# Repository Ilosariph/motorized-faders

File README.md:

# Motorized Fader Controller

RP2040 board (Pico-clone with RTL8720DN WiFi — GP4/GP5 not exposed) + TB6612FNG
motor drivers + Alps motorized faders.

**Two builds exist:**

| | 2-fader breadboard | 4-fader PCB |
|---|---|---|
| Faders | 2x RS60N11M9 (60 mm, 5 kΩ) | 4x RSA0N11M9 (100 mm, 10 kΩ) |
| ADC | RP2040 internal (GP26/27) | MCP3208, 12-bit SPI |
| Drivers | 1x TB6612FNG breakout | 2x TB6612FNG |
| Displays | none | 4x SSD1306 128x64 SPI |
| Buttons | none | 4 per-fader + 2 general, ADC ladder |
| Motor rail | 10 V bench supply | 9 V USB-C PD trigger |
| Docs | this file | [pcb_design.md](docs/pcb_design.md), [firmware.md](docs/firmware.md) |

The wiring below is the **2-fader breadboard** build. For the 4-fader PCB see
[docs/pcb_design.md](docs/pcb_design.md) (hardware) and
[docs/firmware.md](docs/firmware.md) (protocol, mute, displays, buttons).

Firmware in `pico/` is the **4-fader** version. It needs the MCP3208 and will
report `RAIL:fail` without the PD rail; the 2-fader build is kept in git
history.

---

## Wiring

### Power

| From | To | Notes |
|------|----|-------|
| 10V supply + | TB6612FNG VM | Motor power |
| 10V supply − | Common GND | |
| Pico 3.3V (pin 36) | TB6612FNG VCC | Logic power |
| Pico GND (any) | TB6612FNG GND | |
| Pico GND (any) | 10V supply − | Common ground — important! |

The Pico gets power from USB. The 10V supply powers the motors only. All grounds must be connected together.

---

### Fader → TB6612FNG (Motor)

| Fader terminal | Connect to |
|----------------|-----------|
| Terminal 1 (GND) | GND |
| Terminal 3 (3.3V) | Pico 3.3V |
| Terminal A | TB6612FNG AO1 (fader 1) or BO1 (fader 2) |
| Terminal B | TB6612FNG AO2 (fader 1) or BO2 (fader 2) |

If the fader moves in the wrong direction, swap A and B.

---

### Fader → Pico (Sensing)

| Fader terminal | Pico pin | Notes |
|----------------|----------|-------|
| Terminal 2 (wiper) | GP26 (fader 1) | ADC position feedback |
| Terminal 2 (wiper) | GP27 (fader 2) | ADC position feedback |

Terminal T (touch) is unused — the firmware detects move completion from the
PID state machine (deadband + settle timer), not from touch.

---

### TB6612FNG → Pico (Control)

| TB6612FNG pin | Pico pin | Notes |
|---------------|----------|-------|
| AIN1 | GP2 | Fader 1 direction |
| AIN2 | GP3 | Fader 1 direction |
| PWMA | GP6 | Fader 1 speed |
| BIN1 | GP7 | Fader 2 direction |
| BIN2 | GP8 | Fader 2 direction |
| PWMB | GP9 | Fader 2 speed |
| STBY | GP10 | Driver enable |

> **Note:** GP4 and GP5 are skipped — this board does not expose them on the header. If you have a real Raspberry Pi Pico W, you can use the standard GP2–GP8 range instead and update `pico/main.py` accordingly.

---

## One Fader Only

If you only have one fader connected, the firmware still works — fader 2 will sit at its default setpoint (50%) but won't move since nothing is connected. No code changes needed.

Just leave BIN1, BIN2, PWMB, BO1, BO2, and GP27 unconnected.

---

## PC Software

Two interfaces. The **terminal tool** is for bring-up and PID tuning; the
**extension host** is what you actually run day to day.

### Terminal tool

```bash
pip install pyserial
python host/host.py
```

Type `50 75` to set fader 1 to 50% and fader 2 to 75%. Type `50` to set fader 1 only.

If the Pico isn't detected automatically, pass the port explicitly:

```bash
python host/host.py /dev/ttyACM0      # Linux
python host/host.py COM3              # Windows
```

### Extension host

Binds faders to things on the PC. `faders/config.json` declares which
extension owns which fader:

```bash
python -m faders.run
```

With `pulse_sink`, each fader controls a PulseAudio/PipeWire sink: move the
fader to change volume, change it in pavucontrol and the fader follows, and
press the fader's button to mute. The fader's display shows that sink's label
and volume — display content comes from whichever extension owns the fader, so
it describes whatever that fader actually controls.

```json
{"fader": 0, "sink": "sink-music", "min": 0, "max": 100, "label": "Music"}
```

`"source": "source-mic"` in place of `sink` puts an input (e.g. a mic) on the
fader the same way. `label` is optional and defaults to the sink name — worth setting, since real
sink names (`alsa_output.pci-0000_00_1f.3.analog-stereo`) do not fit a 128 px
screen.

More sinks than faders → pages: `fader` 4-7 is page 2, 8-11 page 3 (`G2` +
`F1`/`F4`, `x/y` on the last screen; entries without `fader` fill slots in
list order). The dict form sets `paging` and shares keys between
entries:

```json
"pulse_sink": {
  "paging": true,
  "max": 150,
  "faders": [{"sink": "sink-music"}, {"sink": "sink-comms"}, {"sink": "sink-apps"}]
}
```

`paging`: `"auto"` (default) pages only when a `fader` is past the last one;
`true` always pages; `false` never pages and skips entries past the last
fader. A/B works either way (tap `G2` + `Fn`). Same for `voicemeeter`.

#### Layers and buttons

Plugins are grouped into **layers** that take turns owning the four faders.
Each layer remembers its own fader levels, mutes, screens and creases.
Without a `layers` key every plugin is its own layer (`pulse_sink` → "Audio",
`discord_voice` → "Discord", `home_assistant` → "Home", `voicemeeter` →
"Voicemeeter", `filter_param` → "FX", `media` → "Media"); to choose, list them:

```json
"layers": [
  {"name": "Audio",   "extensions": {"pulse_sink": [...]}},
  {"name": "Discord", "extensions": {"discord_voice": {...}}}
],
```

| Buttons | Action |
|---|---|
| `F1`-`F4` | Mute that fader (`media`: its transport faders' buttons are previous, play/pause, next) |
| `G1` + `F1` / `F4` | Previous / next layer — screens show the name while `G1` is held, faders move on its release |
| `G2` + `Fn` (tap) | A/B position swap |
| `G2` + `F1` / `F4` (hold 0.4 s) | Previous / next page (paged layers: Discord, Home, Media / Audio / Voicemeeter / FX with >4 entries or `"paging": true`) |

#### Discord

`discord_voice` puts the other people in your current voice channel on the
faders: name on the screen, fader = their local volume 0-200%, fader button =
Discord's per-user mute (right-click → Mute; volume untouched). More than four
people → pages, shown as `x/y` on the last screen. Needs the official desktop
client (Vesktop/arRPC lack voice RPC) and your own Discord application:

1. <https://discord.com/developers/applications> → New Application.
2. OAuth2 → copy Client ID and Client Secret, add redirect `http://localhost`.
3. Config: `"discord_voice": {"client_id": "...", "client_secret_file": "/path/to/secret"}`
   (`client_secret` inline also works; keep the file private).
4. Start the host, click **Authorize** in the Discord popup once. The token is
   cached in `~/.local/state/motorized-faders/discord_token.json`.

#### Home Assistant

`home_assistant` binds faders to lights and covers over HA's WebSocket API:

- **Light**: fader = brightness, dragged to the bottom = off; button = off /
  back on at its brightness. Turned off in HA → fader parks (muted).
- **Cover**: `"attribute": "position"` (default) or `"tilt"`. Two faders on
  one blind give position and slat angle. Button = close (0) / restore.
  Covers get one command when the fader comes to rest; the fader follows HA
  once the cover stops moving.

- **Switch** (`switch.*`, `input_boolean.*`): fader bottom = off, above = on;
  button toggles.

Entries fill the faders in order; more than four → pages (hold `G2` + `F1`/`F4`,
`x/y` on the last screen). `null` leaves a fader empty, e.g. to keep a
blind's pair on one page. Needs a long-lived access token (HA profile →
Security):

```json
"home_assistant": {
  "url": "http://homeassistant.local:8123",
  "token_file": "~/.config/motorized-faders/ha-token",
  "faders": [
    {"entity": "light.desk", "label": "Desk"},
    null,
    {"entity": "cover.office", "attribute": "position", "label": "Blinds"},
    {"entity": "cover.office", "attribute": "tilt", "label": "Slats"}
  ]
}
```

`token` inline also works (keep the config private); `"verify_ssl": false`
for a self-signed https URL. `"follow": false` on an entry ignores the values
HA reports for it (the fader alone is the truth) — for a device whose reports
are wrong, e.g. a cover stuck at 1% until its travel is calibrated.

#### Voicemeeter (Windows)

`voicemeeter` binds faders to Voicemeeter (Basic, Banana or Potato) input
strips and output buses, the way `pulse_sink` binds them to sinks: the fader
sets the gain in dB, gain changed in Voicemeeter moves the fader, and the
fader button toggles the strip's/bus's mute (both ways). Screens show the
label set in Voicemeeter (or `label`) and the gain.

```json
"voicemeeter": [
  {"fader": 0, "strip": 0, "label": "Mic"},
  {"fader": 1, "strip": 3},
  {"fader": 3, "bus": 0, "min": -40, "max": 0}
]
```

`strip` / `bus` are 0-based, left to right as in Voicemeeter's window.
`min`/`max` are dB (default -60 / +12, the full slider). More than four
entries → pages, and `"paging"` works as for `pulse_sink`. Talks to the Remote
API DLL shipped with Voicemeeter via ctypes — only `pyserial` needed:

```powershell
pip install pyserial
python -m faders.run --config my-config.json
```

Voicemeeter may start after the host or restart; faders resync when it shows up.

#### PipeWire filter controls

`filter_param` puts controls of plugins running in PipeWire `filter-chain`
modules (an LSP compressor's threshold, ratio, makeup, a gate's threshold ...)
on faders. The fader sets the control, changes made elsewhere move it, the
screen shows the value in real units, and the button bypasses the plugin
(every fader on that plugin parks while it is off). One detent marks the
control's original value.

```json
"filter_param": {
  "faders": [
    {"param": "fx-comp-apps:al", "scale": "db",  "min": -40, "max": 0,  "label": "Apps thr"},
    {"param": "fx-comp-apps:cr", "scale": "log", "min": 1,   "max": 10, "unit": ":1", "label": "Apps ratio"}
  ]
}
```

`param` is `<filter node name>:<LV2 port symbol>`, as `pw-dump` lists it
under the node's `Props`. `scale`: `db` for controls that are linear gains
(range in dB), `log` for times and ratios, `linear` otherwise. More than four
entries → pages. Give it a layer of its own (a layer has one set of pages).

Values set from the faders are saved to
`~/.local/state/motorized-faders/filter_param.json` with the config's original
next to each, and put back when PipeWire reloads the filter (restart, reboot).
A changed value in the PipeWire config wins over a saved one.
`motorized-faders-fx status` lists them, `motorized-faders-fx reset [param ...]`
restores the originals. `"persist": false` turns saving off.

#### Media players

`media` puts whichever player is in use on the faders, on Linux and Windows
alike: Spotify, Plezy, a browser, anything publishing MPRIS (Linux) or a
Windows media session.

| Fader | Control | Button | Screen |
|---|---|---|---|
| 1 | Volume of the player's own stream | Mute | Player, volume |
| 2 | - | Previous | |
| 3 | - | Play / pause | Title, status |
| 4 | - | Next | |

The player playing is selected and stays selected while paused, until another
starts. Several playing at once → one page each (hold `G2` + `F1`/`F4`, `x/y`
on the last screen); the selected one keeps its page while paused. Volume changed in the app moves the fader. `layout` rearranges the
roles (`null` leaves a fader to another plugin on the layer), `players`
restricts to those names, in priority order, and `ignore` excludes some:

```json
"media": {
  "layout": ["volume", "previous", "play_pause", "next"],
  "ignore": ["firefox"]
}
```

Linux needs `playerctl` and `pactl` (the Nix package brings both). Windows needs
two packages next to `pyserial`:

```powershell
pip install "winrt-Windows.Media.Control[all]" pycaw
```

The host survives the Pico being unplugged: it waits for the port to come
back (it may return as a different `ttyACM` node), then replays display text,
A/B badges and creases, and extensions re-seed fader positions and mute via
their `on_connect` hook. Starting without the Pico attached waits the same way.

### NixOS

`flake.nix` exports the package (`nix run .`), a dev shell and
`nixosModules.default`, which runs the host as a systemd **user** service
(plugins like `pulse_sink` need the user's PipeWire session) and grants the
logged-in user the Pico's tty via udev `uaccess`:

```nix
{
  inputs.motorized-faders.url = "github:Ilosariph/motorized-faders";
  # in nixosSystem modules: inputs.motorized-faders.nixosModules.default
  services.motorized-faders = {
    enable = true;
    plugins.pulse_sink = [
      { fader = 0; sink = "sink-master"; max = 100; label = "Master"; }
      { fader = 3; sink = "sink-music"; max = 150; label = "Music"; }
    ];
    plugins.discord_voice = {
      client_id = "1234567890";
      client_secret_file = "/run/secrets/discord-faders";  # not in the store
    };
  };
}
```

`plugins` keys are module names in `faders/extensions/` (checked at eval);
each value is one instance config or a list. `layers` (list of
`{ name; extensions; }`) sets explicit layers. Logs:
`journalctl --user -u motorized-faders -f`.

### Tests

No hardware needed — the fader is simulated and `machine`/`utime` are stubbed:

```bash
python3 tests/run_all.py
```

---

## Files

| File | Description |
|------|-------------|
| `pico/main.py` | MicroPython firmware — copy to Pico as `main.py` |
| `pico/lib/` | Device drivers: MCP3208, buttons, SSD1306, screen layout — **upload with `main.py`** |
| `host/host.py` | PC terminal interface (calibrated 0–100% display) |
| `host/host_raw.py` | Raw 16-bit ADC viewer for wiring diagnostics |
| `faders/` | Extension host — serial transport, button/mute dispatch, plugins |
| `faders/extensions/pulse_sink.py` | Binds a fader to a PulseAudio/PipeWire sink |
| `faders/extensions/discord_voice.py` | Voice-channel users on the faders: volume, mute, pages |
| `faders/extensions/home_assistant.py` | HA lights (brightness, on/off) and covers (position, tilt), paged |
| `faders/extensions/voicemeeter.py` | Binds a fader to a Voicemeeter strip or bus (Windows) |
| `faders/extensions/filter_param.py` | PipeWire filter-chain plugin controls (compressor, gate ...), saved across restarts |
| `faders/extensions/media.py` | Current media player: per-app volume, mute, play/pause, next, previous (Linux, Windows) |
| `tests/` | Test suites — run `python3 tests/run_all.py`, no hardware required |
| `docs/upload.md` | How to flash firmware to the Pico (Thonny + mpremote) |
| `docs/pid_tuning.md` | How to tune the PID controller |
| `docs/firmware.md` | 4-fader firmware — protocol, buttons, mute, displays |
| `docs/pcb_design.md` | 4-fader PCB design — ADC choice, TB6612FNG, BOM |
| `docs/modular_design.md` | Future modular expansion plan (RP2040-Zero modules) |

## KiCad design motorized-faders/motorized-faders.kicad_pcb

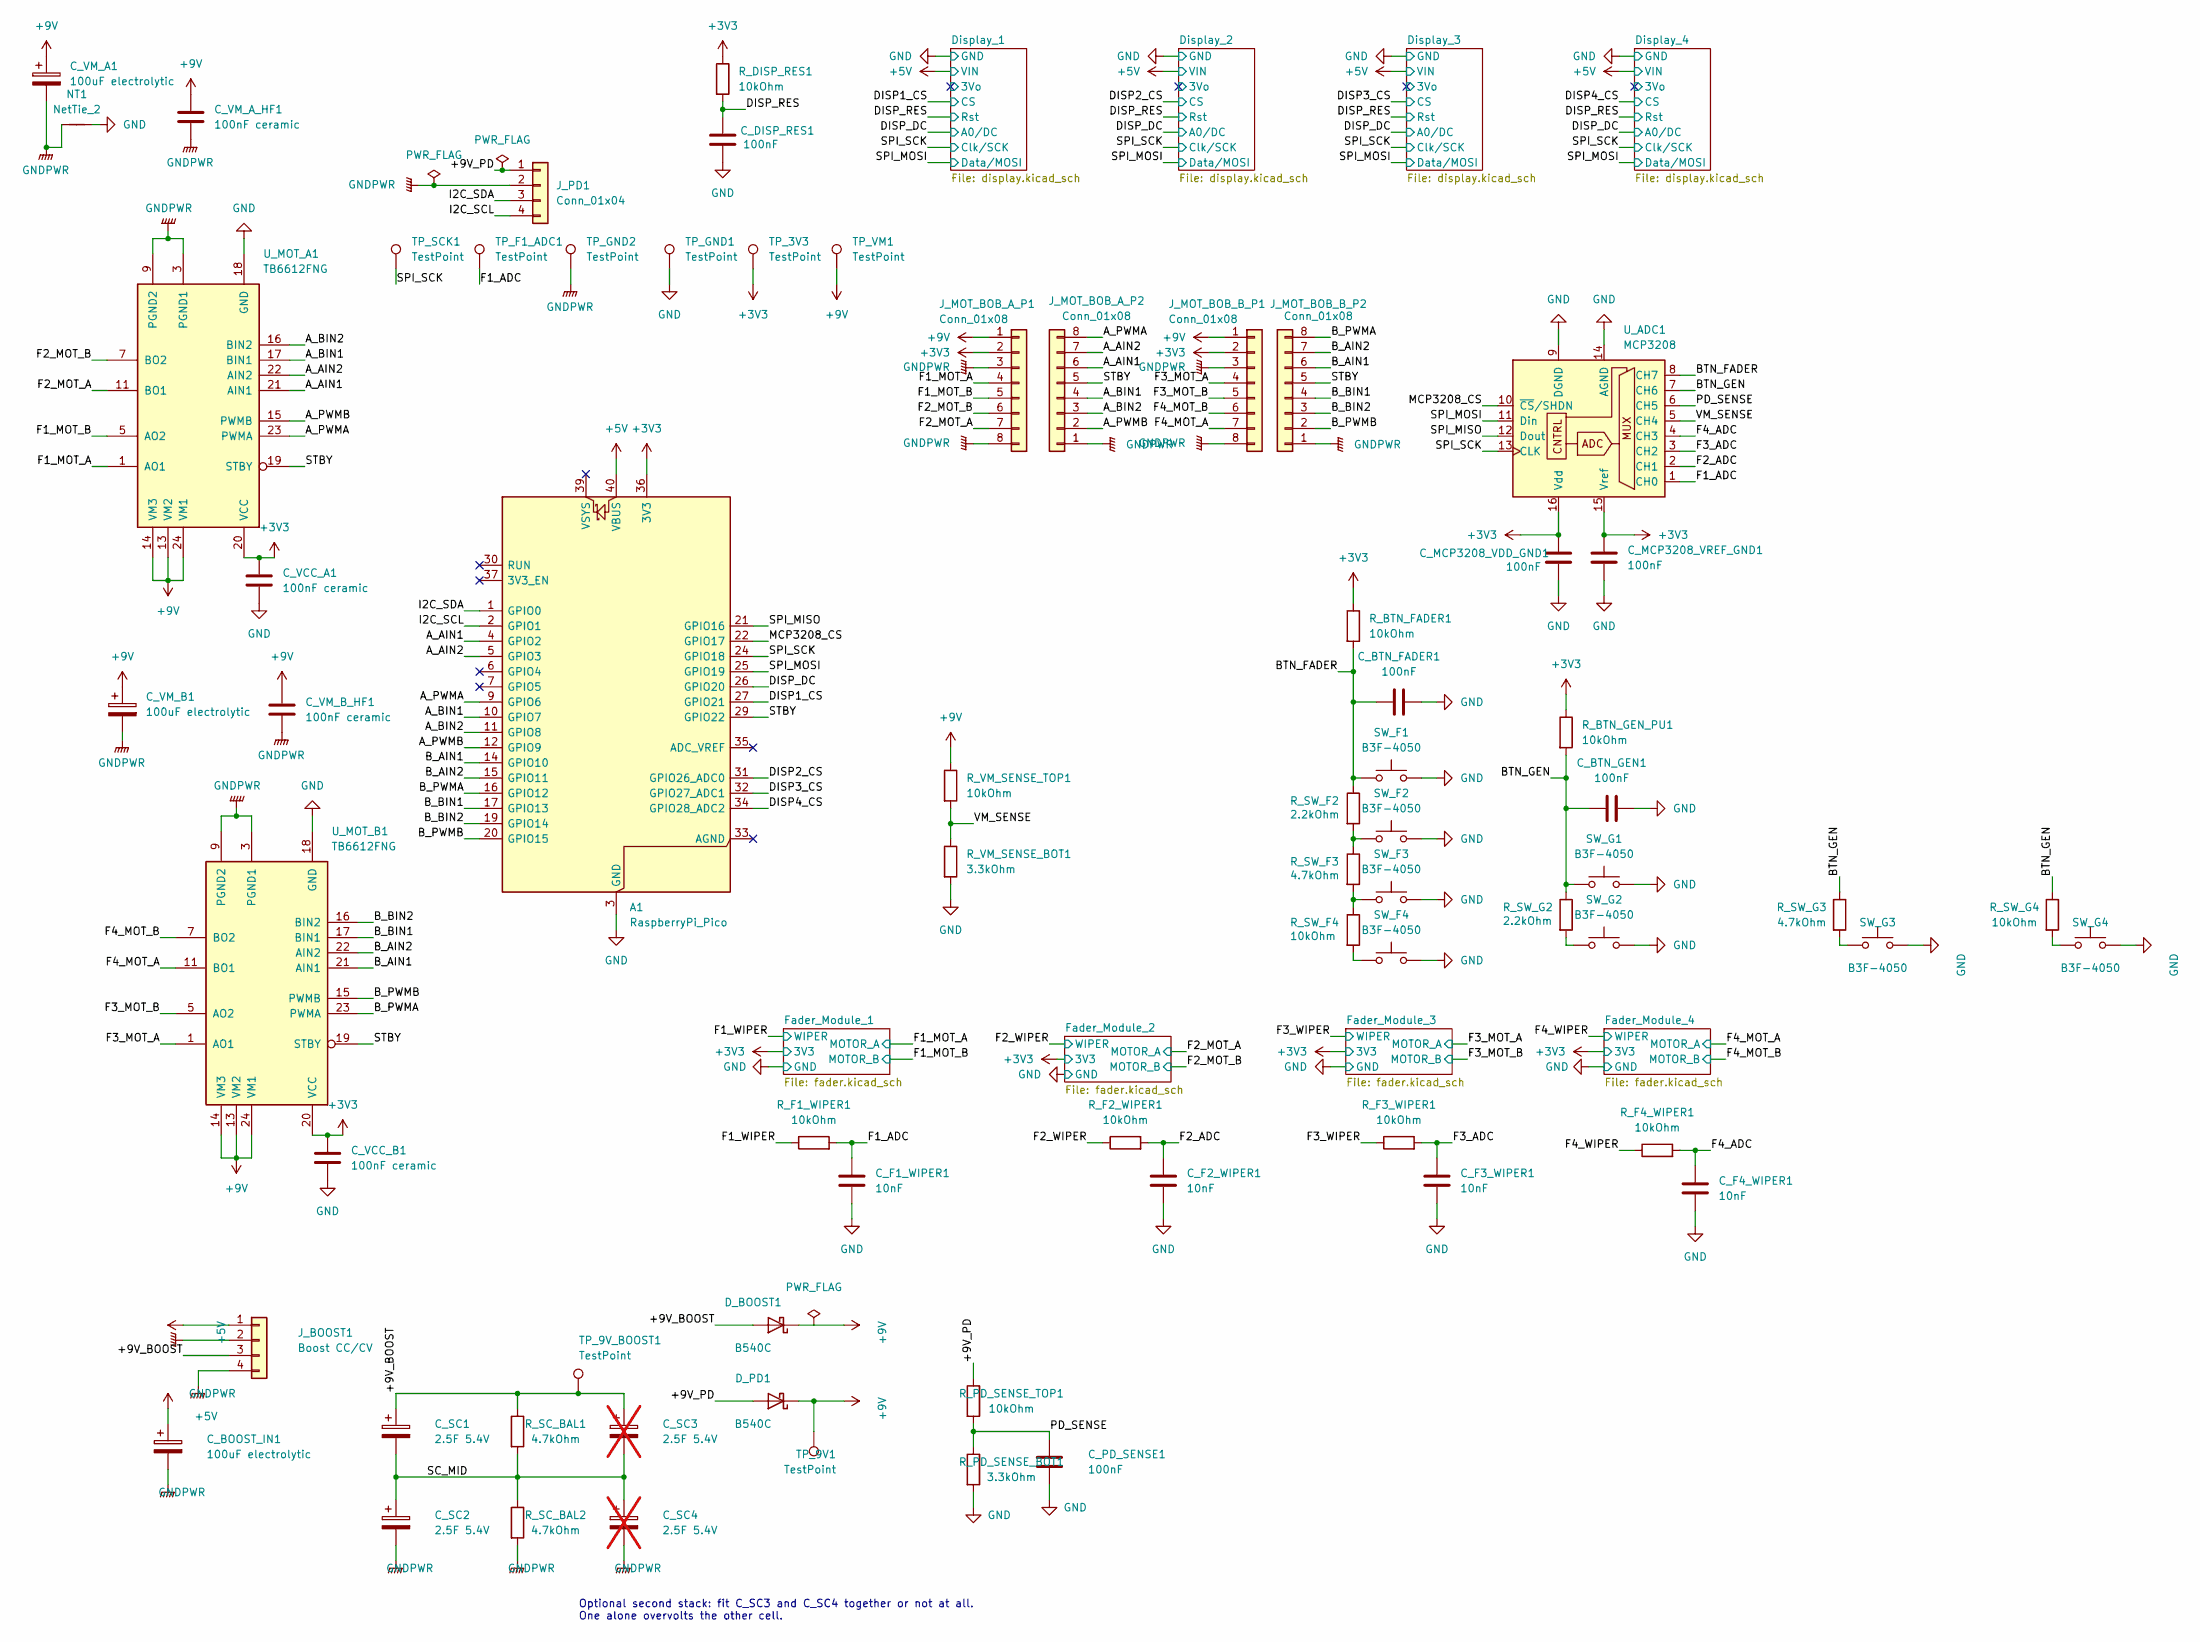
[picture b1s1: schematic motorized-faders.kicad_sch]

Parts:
A1: RaspberryPi_Pico; RaspberryPi_Pico_Common_THT
C_BOOST_IN1: 100uF electrolytic; CP_Radial_D8.0mm_P5.00mm
C_BTN_FADER1: 100nF; C_0805_2012Metric
C_BTN_GEN1: 100nF; C_0805_2012Metric
C_DISP_RES1: 100nF; C_0805_2012Metric
C_F1_WIPER1, C_F2_WIPER1, C_F3_WIPER1, C_F4_WIPER1: 10nF; C_0805_2012Metric
C_MCP3208_VDD_GND1, C_MCP3208_VREF_GND1: 100nF; C_0805_2012Metric
C_PD_SENSE1: 100nF; C_0805_2012Metric
C_SC1, C_SC2: 2.5F 5.4V; Supercap_Eaton_PHV-5R4V255-R
C_SC3, C_SC4: 2.5F 5.4V; Supercap_Eaton_PHV-5R4V255-R; not fitted
C_VCC_A1: 100nF ceramic; C_0805_2012Metric
C_VCC_B1: 100nF ceramic; C_0805_2012Metric
C_VM_A1: 100uF electrolytic; CP_Radial_D8.0mm_P5.00mm
C_VM_A_HF1: 100nF ceramic; C_0805_2012Metric
C_VM_B1: 100uF electrolytic; CP_Radial_D8.0mm_P5.00mm
C_VM_B_HF1: 100nF ceramic; C_0805_2012Metric
D_BOOST1: B540C; D_SMC_Handsoldering
D_PD1: B540C; D_SMC_Handsoldering
J_BOOST1: Boost CC/CV; JST_XH_B4B-XH-A_1x04_P2.50mm_Vertical
J_MOT_BOB_A_P1, J_MOT_BOB_A_P2: Conn_01x08; PinHeader_1x08_P2.54mm_Vertical
J_MOT_BOB_B_P1, J_MOT_BOB_B_P2: Conn_01x08; PinHeader_1x08_P2.54mm_Vertical
J_PD1: Conn_01x04; JST_XH_B4B-XH-A_1x04_P2.50mm_Vertical
NT1: NetTie_2; NetTie-2_SMD_Pad2.0mm
R_BTN_FADER1: 10kOhm; R_0805_2012Metric
R_BTN_GEN_PU1: 10kOhm; R_0805_2012Metric
R_DISP_RES1: 10kOhm; R_0805_2012Metric
R_F1_WIPER1, R_F2_WIPER1, R_F3_WIPER1, R_F4_WIPER1: 10kOhm; R_0805_2012Metric
R_PD_SENSE_BOT1: 3.3kOhm; R_0805_2012Metric
R_PD_SENSE_TOP1: 10kOhm; R_0805_2012Metric
R_SC_BAL1, R_SC_BAL2: 4.7kOhm; R_0805_2012Metric
R_SW_F2: 2.2kOhm; R_0805_2012Metric
R_SW_F3: 4.7kOhm; R_0805_2012Metric
R_SW_F4: 10kOhm; R_0805_2012Metric
R_SW_G2: 2.2kOhm; R_0805_2012Metric
R_SW_G3: 4.7kOhm; R_0805_2012Metric
R_SW_G4: 10kOhm; R_0805_2012Metric
R_VM_SENSE_BOT1: 3.3kOhm; R_0805_2012Metric
R_VM_SENSE_TOP1: 10kOhm; R_0805_2012Metric
SW_F1, SW_F2, SW_F3, SW_F4: B3F-4050; JST_XH_B2B-XH-A_1x02_P2.50mm_Vertical
SW_G1, SW_G2, SW_G3, SW_G4: B3F-4050; JST_XH_B2B-XH-A_1x02_P2.50mm_Vertical
TP_3V3, TP_9V1, TP_9V_BOOST1: TestPoint; TestPoint_THTPad_D1.5mm_Drill0.7mm
TP_F1_ADC1: TestPoint; TestPoint_THTPad_D1.5mm_Drill0.7mm
TP_GND1, TP_GND2: TestPoint; TestPoint_THTPad_D1.5mm_Drill0.7mm
TP_SCK1: TestPoint; TestPoint_THTPad_D1.5mm_Drill0.7mm
TP_VM1: TestPoint; TestPoint_THTPad_D1.5mm_Drill0.7mm
U_ADC1: MCP3208; DIP-16_W7.62mm
U_MOT_A1: TB6612FNG; SSOP-24_5.3x8.2mm_P0.65mm
U_MOT_B1: TB6612FNG; SSOP-24_5.3x8.2mm_P0.65mm

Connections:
+3V3: A1.36 (3V3), C_MCP3208_VDD_GND1.1, C_MCP3208_VREF_GND1.1, C_VCC_A1.1, C_VCC_B1.1, J_MOT_BOB_A_P1.2, J_MOT_BOB_B_P1.2, R_BTN_FADER1.1, R_BTN_GEN_PU1.1, R_DISP_RES1.1, TP_3V3.1 (1_1), U_ADC1.15 (Vref), U_ADC1.16 (Vdd), U_MOT_A1.20 (VCC), U_MOT_B1.20 (VCC); also elsewhere on the board
+5V: A1.40 (VBUS), C_BOOST_IN1.1, J_BOOST1.1; also elsewhere on the board
+9V: C_VM_A1.1, C_VM_A_HF1.1, C_VM_B1.1, C_VM_B_HF1.1, D_BOOST1.1 (K), D_PD1.1 (K), J_MOT_BOB_A_P1.1, J_MOT_BOB_B_P1.1, R_VM_SENSE_TOP1.1, TP_9V1.1 (1_1), TP_VM1.1 (1_1), U_MOT_A1.13 (VM2), U_MOT_A1.14 (VM3), U_MOT_A1.24 (VM1), U_MOT_B1.13 (VM2), U_MOT_B1.14 (VM3), U_MOT_B1.24 (VM1)
/+9V_BOOST: C_SC1.1, C_SC3.1, D_BOOST1.2 (A), J_BOOST1.3, R_SC_BAL1.1, TP_9V_BOOST1.1 (1_1)
/+9V_PD: D_PD1.2 (A), J_PD1.1, R_PD_SENSE_TOP1.1
/A_AIN1: A1.4 (GPIO2), J_MOT_BOB_A_P2.6, U_MOT_A1.21 (AIN1)
/A_AIN2: A1.5 (GPIO3), J_MOT_BOB_A_P2.7, U_MOT_A1.22 (AIN2)
/A_BIN1: A1.10 (GPIO7), J_MOT_BOB_A_P2.4, U_MOT_A1.17 (BIN1)
/A_BIN2: A1.11 (GPIO8), J_MOT_BOB_A_P2.3, U_MOT_A1.16 (BIN2)
/A_PWMA: A1.9 (GPIO6), J_MOT_BOB_A_P2.8, U_MOT_A1.23 (PWMA)
/A_PWMB: A1.12 (GPIO9), J_MOT_BOB_A_P2.2, U_MOT_A1.15 (PWMB)
/BTN_FADER: C_BTN_FADER1.1, R_BTN_FADER1.2, R_SW_F2.1, SW_F1.1, U_ADC1.8 (CH7)
/BTN_GEN: C_BTN_GEN1.1, R_BTN_GEN_PU1.2, R_SW_G2.1, R_SW_G3.1, R_SW_G4.1, SW_G1.1, U_ADC1.7 (CH6)
/B_AIN1: A1.14 (GPIO10), J_MOT_BOB_B_P2.6, U_MOT_B1.21 (AIN1)
/B_AIN2: A1.15 (GPIO11), J_MOT_BOB_B_P2.7, U_MOT_B1.22 (AIN2)
/B_BIN1: A1.17 (GPIO13), J_MOT_BOB_B_P2.4, U_MOT_B1.17 (BIN1)
/B_BIN2: A1.19 (GPIO14), J_MOT_BOB_B_P2.3, U_MOT_B1.16 (BIN2)
/B_PWMA: A1.16 (GPIO12), J_MOT_BOB_B_P2.8, U_MOT_B1.23 (PWMA)
/B_PWMB: A1.20 (GPIO15), J_MOT_BOB_B_P2.2, U_MOT_B1.15 (PWMB)
/DISP1_CS: A1.27 (GPIO21); also elsewhere on the board
/DISP2_CS: A1.31 (GPIO26_ADC0); also elsewhere on the board
/DISP3_CS: A1.32 (GPIO27_ADC1); also elsewhere on the board
/DISP4_CS: A1.34 (GPIO28_ADC2); also elsewhere on the board
/DISP_DC: A1.26 (GPIO20); also elsewhere on the board
/DISP_RES: C_DISP_RES1.2, R_DISP_RES1.2; also elsewhere on the board
/F1_ADC: C_F1_WIPER1.1, R_F1_WIPER1.2, TP_F1_ADC1.1 (1_1), U_ADC1.1 (CH0)
/F1_MOT_A: J_MOT_BOB_A_P1.4, U_MOT_A1.1 (AO1), U_MOT_A1.2 (AO1); also elsewhere on the board
/F1_MOT_B: J_MOT_BOB_A_P1.5, U_MOT_A1.5 (AO2), U_MOT_A1.6 (AO2); also elsewhere on the board
/F1_WIPER: R_F1_WIPER1.1; also elsewhere on the board
/F2_ADC: C_F2_WIPER1.1, R_F2_WIPER1.2, U_ADC1.2 (CH1)
/F2_MOT_A: J_MOT_BOB_A_P1.7, U_MOT_A1.11 (BO1), U_MOT_A1.12 (BO1); also elsewhere on the board
/F2_MOT_B: J_MOT_BOB_A_P1.6, U_MOT_A1.7 (BO2), U_MOT_A1.8 (BO2); also elsewhere on the board
/F2_WIPER: R_F2_WIPER1.1; also elsewhere on the board
/F3_ADC: C_F3_WIPER1.1, R_F3_WIPER1.2, U_ADC1.3 (CH2)
/F3_MOT_A: J_MOT_BOB_B_P1.4, U_MOT_B1.1 (AO1), U_MOT_B1.2 (AO1); also elsewhere on the board
/F3_MOT_B: J_MOT_BOB_B_P1.5, U_MOT_B1.5 (AO2), U_MOT_B1.6 (AO2); also elsewhere on the board
/F3_WIPER: R_F3_WIPER1.1; also elsewhere on the board
/F4_ADC: C_F4_WIPER1.1, R_F4_WIPER1.2, U_ADC1.4 (CH3)
/F4_MOT_A: J_MOT_BOB_B_P1.7, U_MOT_B1.11 (BO1), U_MOT_B1.12 (BO1); also elsewhere on the board
/F4_MOT_B: J_MOT_BOB_B_P1.6, U_MOT_B1.7 (BO2), U_MOT_B1.8 (BO2); also elsewhere on the board
/F4_WIPER: R_F4_WIPER1.1; also elsewhere on the board
/I2C_SCL: A1.2 (GPIO1), J_PD1.4
/I2C_SDA: A1.1 (GPIO0), J_PD1.3
/MCP3208_CS: A1.22 (GPIO17), U_ADC1.10 (~CS/SHDN)
/PD_SENSE: C_PD_SENSE1.1, R_PD_SENSE_BOT1.1, R_PD_SENSE_TOP1.2, U_ADC1.6 (CH5)
/SC_MID: C_SC1.2, C_SC2.1, C_SC3.2, C_SC4.1, R_SC_BAL1.2, R_SC_BAL2.1
/SPI_MISO: A1.21 (GPIO16), U_ADC1.12 (Dout)
/SPI_MOSI: A1.25 (GPIO19), U_ADC1.11 (Din); also elsewhere on the board
/SPI_SCK: A1.24 (GPIO18), TP_SCK1.1 (1_1), U_ADC1.13 (CLK); also elsewhere on the board
/STBY: A1.29 (GPIO22), J_MOT_BOB_A_P2.5, J_MOT_BOB_B_P2.5, U_MOT_A1.19 (STBY), U_MOT_B1.19 (STBY)
/VM_SENSE: R_VM_SENSE_BOT1.1, R_VM_SENSE_TOP1.2, U_ADC1.5 (CH4)
GND: A1.3 (GND), A1.8 (GND), A1.13 (GND), A1.18 (GND), A1.23 (GND), A1.28 (GND), A1.38 (GND), C_BTN_FADER1.2, C_BTN_GEN1.2, C_DISP_RES1.1, C_F1_WIPER1.2, C_F2_WIPER1.2, C_F3_WIPER1.2, C_F4_WIPER1.2, C_MCP3208_VDD_GND1.2, C_MCP3208_VREF_GND1.2, C_PD_SENSE1.2, C_VCC_A1.2, C_VCC_B1.2, NT1.2, R_PD_SENSE_BOT1.2, R_VM_SENSE_BOT1.2, SW_F1.2, SW_F2.2, SW_F3.2, SW_F4.2, SW_G1.2, SW_G2.2, SW_G3.2, SW_G4.2, TP_GND1.1 (1_1), U_ADC1.9 (DGND), U_ADC1.14 (AGND), U_MOT_A1.18 (GND), U_MOT_B1.18 (GND); also elsewhere on the board
GNDPWR: C_BOOST_IN1.2, C_SC2.2, C_SC4.2, C_VM_A1.2, C_VM_A_HF1.2, C_VM_B1.2, C_VM_B_HF1.2, J_BOOST1.2, J_BOOST1.4, J_MOT_BOB_A_P1.3, J_MOT_BOB_A_P1.8, J_MOT_BOB_A_P2.1, J_MOT_BOB_B_P1.3, J_MOT_BOB_B_P1.8, J_MOT_BOB_B_P2.1, J_PD1.2, NT1.1, R_SC_BAL2.2, TP_GND2.1 (1_1), U_MOT_A1.3 (PGND1), U_MOT_A1.4 (PGND1), U_MOT_A1.9 (PGND2), U_MOT_A1.10 (PGND2), U_MOT_B1.3 (PGND1), U_MOT_B1.4 (PGND1), U_MOT_B1.9 (PGND2), U_MOT_B1.10 (PGND2)
unnamed: R_SW_F2.2, R_SW_F3.1, SW_F2.1
unnamed: R_SW_F3.2, R_SW_F4.1, SW_F3.1
unnamed: R_SW_F4.2, SW_F4.1
unnamed: R_SW_G2.2, SW_G2.1
unnamed: R_SW_G3.2, SW_G3.1
unnamed: R_SW_G4.2, SW_G4.1

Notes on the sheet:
Optional second stack: fit C_SC3 and C_SC4 together or not at all. One alone overvolts the other cell.

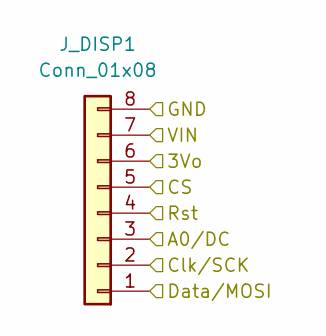
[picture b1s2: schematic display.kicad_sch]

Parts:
J_DISP1: Conn_01x08; JST_XH_B8B-XH-A_1x08_P2.50mm_Vertical

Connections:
+5V: J_DISP1.7; also elsewhere on the board
/DISP1_CS: J_DISP1.5; also elsewhere on the board
/DISP_DC: J_DISP1.3; also elsewhere on the board
/DISP_RES: J_DISP1.4; also elsewhere on the board
/Display_1/3Vo: J_DISP1.6
/SPI_MOSI: J_DISP1.1; also elsewhere on the board
/SPI_SCK: J_DISP1.2; also elsewhere on the board
GND: J_DISP1.8; also elsewhere on the board

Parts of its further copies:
J_DISP2, J_DISP3, J_DISP4: Conn_01x08; JST_XH_B8B-XH-A_1x08_P2.50mm_Vertical

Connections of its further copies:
+5V: J_DISP2.7, J_DISP3.7, J_DISP4.7; also elsewhere on the board
/DISP2_CS: J_DISP2.5; also elsewhere on the board
/DISP3_CS: J_DISP3.5; also elsewhere on the board
/DISP4_CS: J_DISP4.5; also elsewhere on the board
/DISP_DC: J_DISP2.3, J_DISP3.3, J_DISP4.3; also elsewhere on the board
/DISP_RES: J_DISP2.4, J_DISP3.4, J_DISP4.4; also elsewhere on the board
/Display_2/3Vo: J_DISP2.6
/Display_3/3Vo: J_DISP3.6
/Display_4/3Vo: J_DISP4.6
/SPI_MOSI: J_DISP2.1, J_DISP3.1, J_DISP4.1; also elsewhere on the board
/SPI_SCK: J_DISP2.2, J_DISP3.2, J_DISP4.2; also elsewhere on the board
GND: J_DISP2.8, J_DISP3.8, J_DISP4.8; also elsewhere on the board

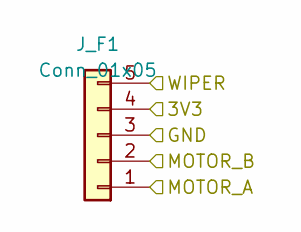
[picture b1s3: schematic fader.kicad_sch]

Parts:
J_F1: Conn_01x05; JST_XH_B5B-XH-A_1x05_P2.50mm_Vertical

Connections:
+3V3: J_F1.4; also elsewhere on the board
/F1_MOT_A: J_F1.1; also elsewhere on the board
/F1_MOT_B: J_F1.2; also elsewhere on the board
/F1_WIPER: J_F1.5; also elsewhere on the board
GND: J_F1.3; also elsewhere on the board

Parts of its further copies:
J_F2, J_F3, J_F4: Conn_01x05; JST_XH_B5B-XH-A_1x05_P2.50mm_Vertical

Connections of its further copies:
+3V3: J_F2.4, J_F3.4, J_F4.4; also elsewhere on the board
/F2_MOT_A: J_F2.1; also elsewhere on the board
/F2_MOT_B: J_F2.2; also elsewhere on the board
/F2_WIPER: J_F2.5; also elsewhere on the board
/F3_MOT_A: J_F3.1; also elsewhere on the board
/F3_MOT_B: J_F3.2; also elsewhere on the board
/F3_WIPER: J_F3.5; also elsewhere on the board
/F4_MOT_A: J_F4.1; also elsewhere on the board
/F4_MOT_B: J_F4.2; also elsewhere on the board
/F4_WIPER: J_F4.5; also elsewhere on the board
GND: J_F2.3, J_F3.3, J_F4.3; also elsewhere on the board

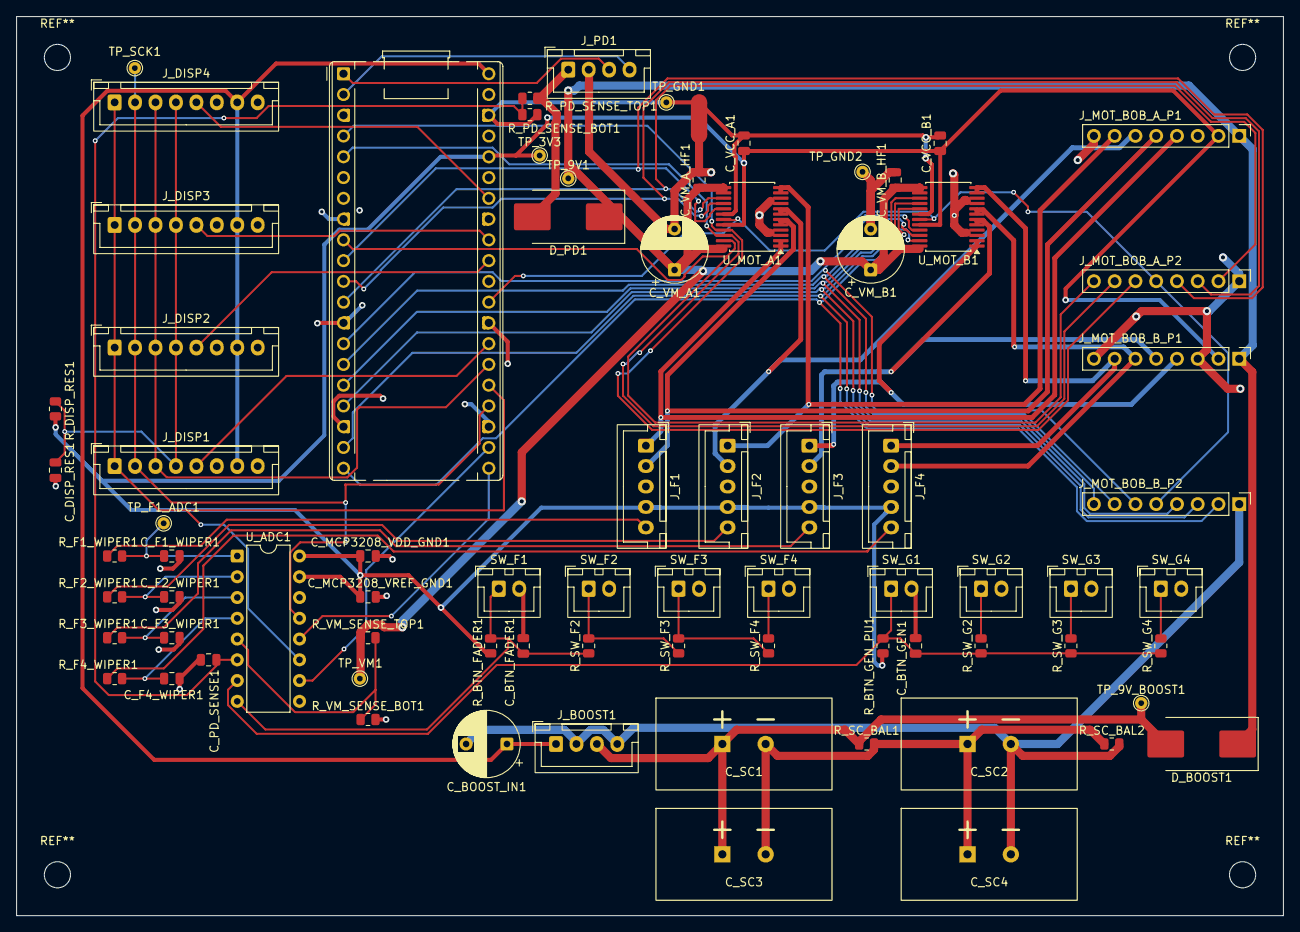
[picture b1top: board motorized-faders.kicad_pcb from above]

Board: 2 copper layers, 155.0 x 110.0 mm, 77 parts (0 on the bottom side), 59 nets.

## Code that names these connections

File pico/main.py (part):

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# Pin map — validated in docs/pcb_design.md against two hardware constraints:
# SPI0 on legal pins, and the four PWM outputs on four distinct slices.
# ---------------------------------------------------------------------------
PIN_STBY = 22          # shared by both TB6612FNG

# (in1, in2, pwm) per fader. PWM pins are GP6/9/12/15 -> slices 3/4/6/7.
MOTOR_PINS = (
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    (13, 14, 15),   # fader 4 — driver B channel B
)

PIN_SPI_SCK = 18
PIN_SPI_MOSI = 19
PIN_SPI_MISO = 16
PIN_MCP_CS = 17
PIN_DISP_DC = 20
DISPLAY_CS_PINS = (21, 26, 27, 28)

# ~1 MHz: safe for the MCP3208 at 3.3 V, trivial for the SSD1306. A full
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

class MotorDriver:
    def __init__(self, in1, in2, pwm_pin, stby):
        from machine import PWM
        self.in1 = Pin(in1, Pin.OUT)
        self.in2 = Pin(in2, Pin.OUT)
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
def _build_screens(spi):
    """Bring up the four displays. A missing display must not kill the rig."""
    dc = Pin(PIN_DISP_DC, Pin.OUT)
    # The shared RC reset on DISP_RES needs to release before the first
    # command reaches any controller.
    _delay(DISPLAY_RESET_MS)
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    # STBY starts LOW: the H-bridges stay disabled until the VM rail is
    # verified. The 10k pull-up defines the pin during MCU reset, before this
    # line runs; from here on firmware owns it.
    stby = Pin(PIN_STBY, Pin.OUT)
    stby.value(0)

    spi = SPI(
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        baudrate=SPI_BAUDRATE,
        polarity=0,
        phase=0,
        sck=Pin(PIN_SPI_SCK),
        mosi=Pin(PIN_SPI_MOSI),
        miso=Pin(PIN_SPI_MISO),
    )
    adc = MCP3208(spi, Pin(PIN_MCP_CS, Pin.OUT))

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            faders.append(None)
            continue
        in1, in2, pwm_pin = MOTOR_PINS[idx]
        motor = MotorDriver(in1, in2, pwm_pin, stby)
        channel = ADC_CH_FADER[idx]
        faders.append(
            FaderPID(
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
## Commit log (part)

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2026-06-21 Initial working state
2026-06-21 work without touch pin
2026-06-21 fader controller with extension system, basic extension for pulseaudio
2026-06-23 add automated PID tuner (tuning/) with runtime PID: command
    Closed-loop step-response tuner that runs on the host, pushes
    candidate gains to the Pico via a new PID:kp,ki,kd command, scores
    the resulting traces (IAE + overshoot + settling + ss-error) and
    searches the gain space with Twiddle, seeded from the existing
    KP/KI/KD in pico/main.py.
    Step suite spans tiny (5%), small (20%), medium (60%), full-travel
2026-06-29 fix: touch detection needs external pull-down on T pin
    The Alps RS60N11M9 T terminal doesn't short to GND when touched — it
    couples 50/60Hz mains hum through the user's body. The previous wiring
    (internal pull-up, expecting LOW = touched) made detection impossible:
    the pin just sat at 3.3V regardless.
    Hardware: add a 1MΩ resistor between each T pin and GND. Documented in
    the README wiring section and the modular-design BOM.
2026-06-29 feat: touch override aborts motor movement, streams user position
    Adds a USER state to the Pico's per-fader state machine. Touching the
    fader while it is MOVING or SETTLING transitions it to USER: the motor
    is stopped immediately, the PID is disengaged, and the engaged 20 Hz
    heartbeat keeps streaming POS: so the host tracks the user's hand.
    On release the setpoint is snapped to the user's final position and the
    state falls through to IDLE — the existing idle behaviour
2026-06-29 enable second fader
